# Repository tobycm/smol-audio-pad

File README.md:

# smol audio pad

a small keypad equipped with a xiao nrf52840 and a battery for portable and wireless usage, with a rotary encoder for input freedom!!

## PCB

## CAD

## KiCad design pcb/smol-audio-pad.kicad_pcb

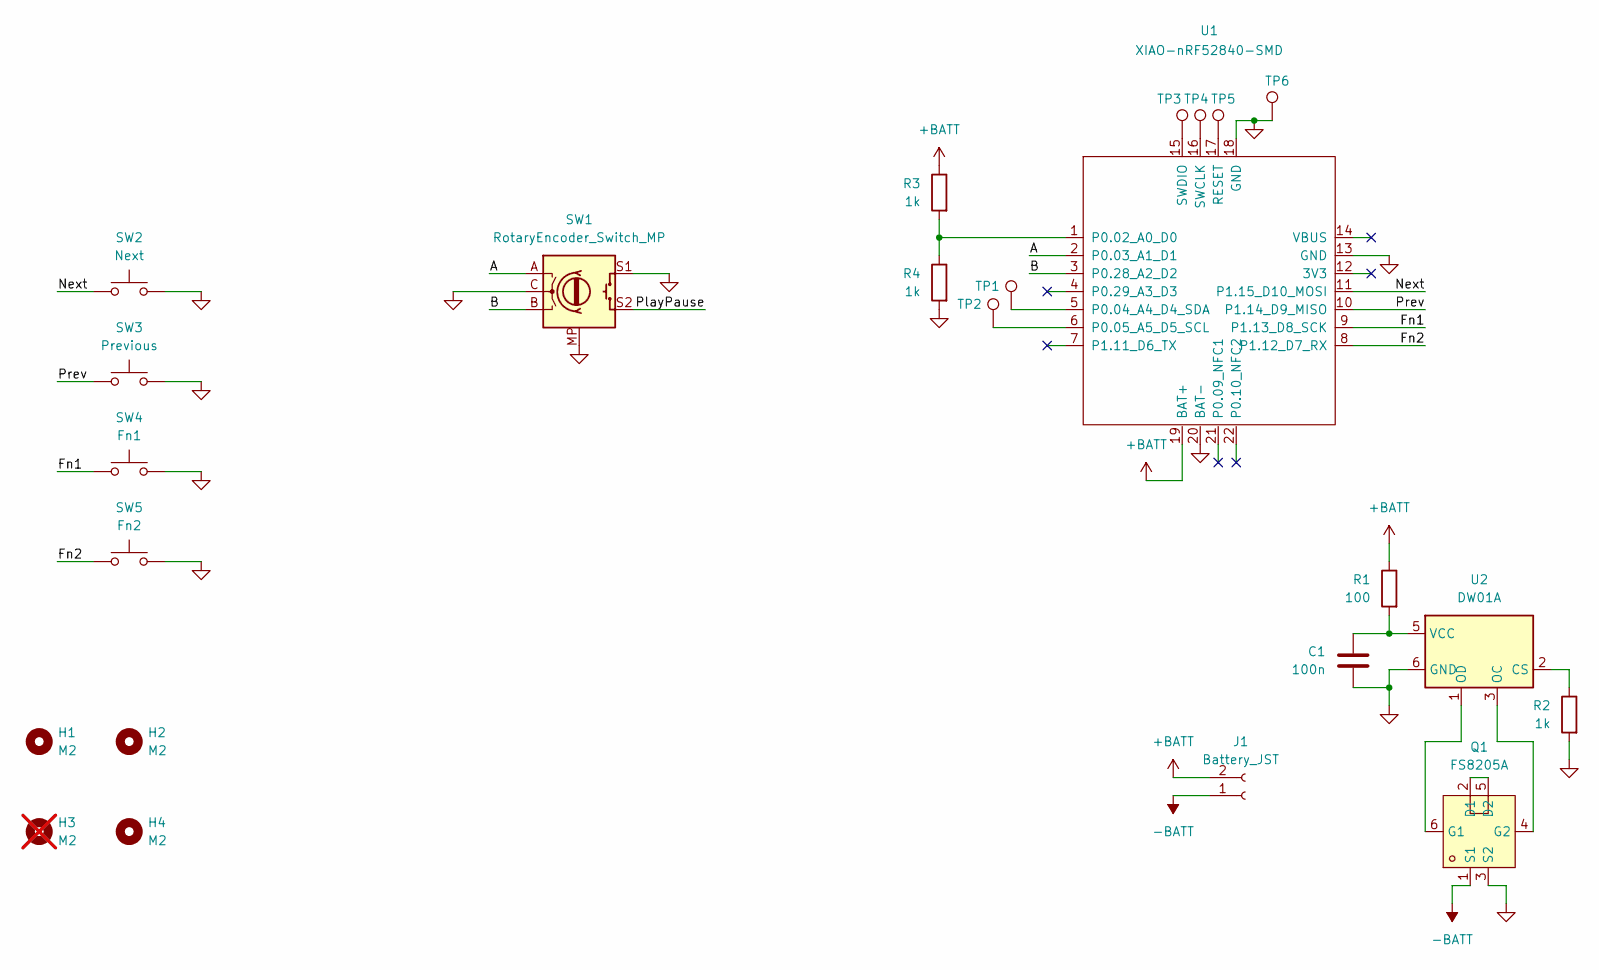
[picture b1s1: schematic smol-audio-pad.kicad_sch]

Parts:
C1: 100n; C_0603_1608Metric
H1, H2, H4: M2; MountingHole_2.2mm_M2_Pad
H3: M2; MountingHole_2.2mm_M2_Pad; not fitted
J1: Battery_JST; JST_PH_S2B-PH-K_1x02_P2.00mm_Horizontal
Q1: FS8205A; SOT-23-6; MPN FS8205A
R1: 100; R_0603_1608Metric
R2, R3, R4: 1k; R_0603_1608Metric
SW1: RotaryEncoder_Switch_MP; XDCR_PEC12R-4220F-S0024
SW2: Next; SW_Cherry_MX_1.00u_PCB
SW3: Previous; SW_Cherry_MX_1.00u_PCB
SW4: Fn1; SW_Cherry_MX_1.00u_PCB
SW5: Fn2; SW_Cherry_MX_1.00u_PCB
TP1, TP2, TP3, TP4, TP5, TP6: TestPoint; TestPoint_Pad_D2.0mm
U1: XIAO-nRF52840-SMD
U2: DW01A; SOT-23-6

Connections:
+BATT: J1.2, R1.1, R3.1, U1.19 (BAT+)
-BATT: J1.1, Q1.1 (S1)
/A: SW1.A, U1.2 (P0.03_A1_D1)
/B: SW1.B, U1.3 (P0.28_A2_D2)
/Fn1: SW4.1, U1.9 (P1.13_D8_SCK)
/Fn2: SW5.1, U1.8 (P1.12_D7_RX)
/Next: SW2.1, U1.11 (P1.15_D10_MOSI)
/PlayPause: SW1.S2
/Prev: SW3.1, U1.10 (P1.14_D9_MISO)
GND: C1.2, Q1.3 (S2), R2.2, R4.2, SW1.C, SW1.MP, SW1.S1, SW2.2, SW3.2, SW4.2, SW5.2, TP6.1 (1_1), U1.13 (GND), U1.18 (GND), U1.20 (BAT-), U2.6 (GND)
unnamed: Q1.2 (D1), Q1.5 (D2)
unnamed: Q1.6 (G1), U2.1 (OD)
unnamed: Q1.4 (G2), U2.3 (OC)
unnamed: R3.2, R4.1, U1.1 (P0.02_A0_D0)
unnamed: TP1.1 (1_1), U1.5 (P0.04_A4_D4_SDA)
unnamed: TP2.1 (1_1), U1.6 (P0.05_A5_D5_SCL)
unnamed: TP5.1 (1_1), U1.17 (RESET)
unnamed: TP4.1 (1_1), U1.16 (SWCLK)
unnamed: TP3.1 (1_1), U1.15 (SWDIO)
unnamed: R2.1, U2.2 (CS)
unnamed: C1.1, R1.2, U2.5 (VCC)

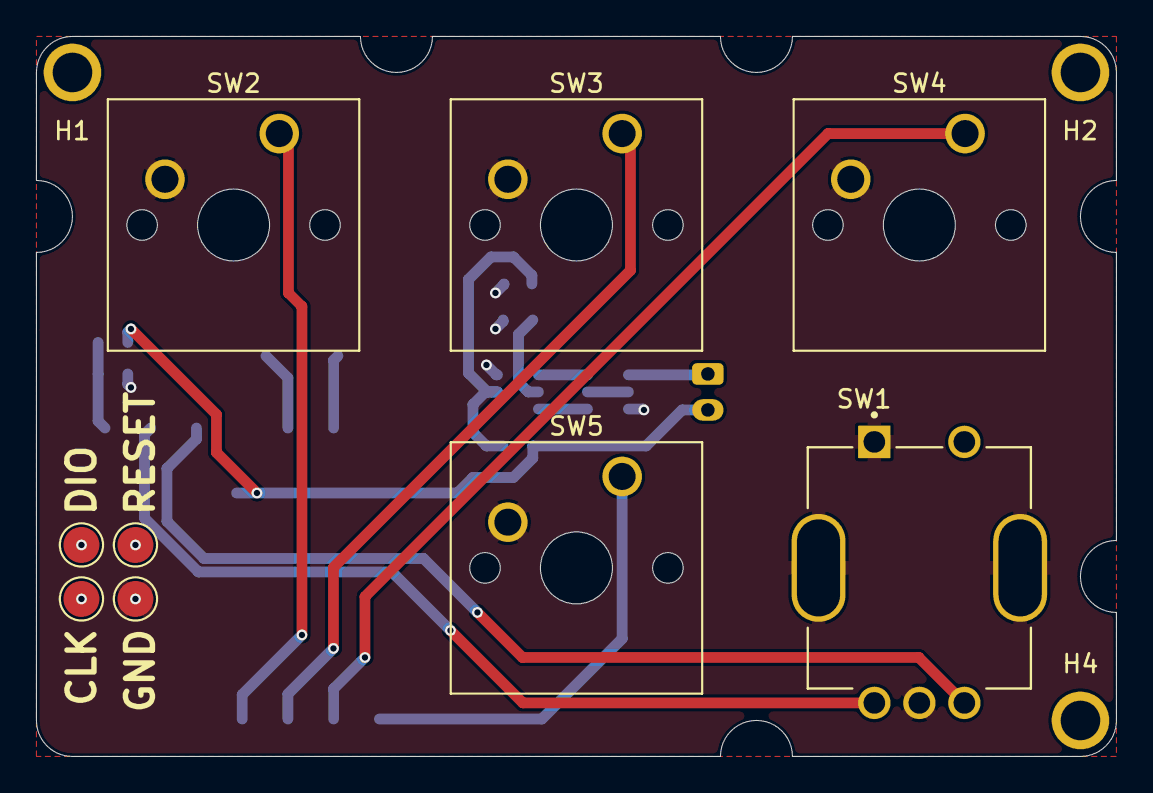
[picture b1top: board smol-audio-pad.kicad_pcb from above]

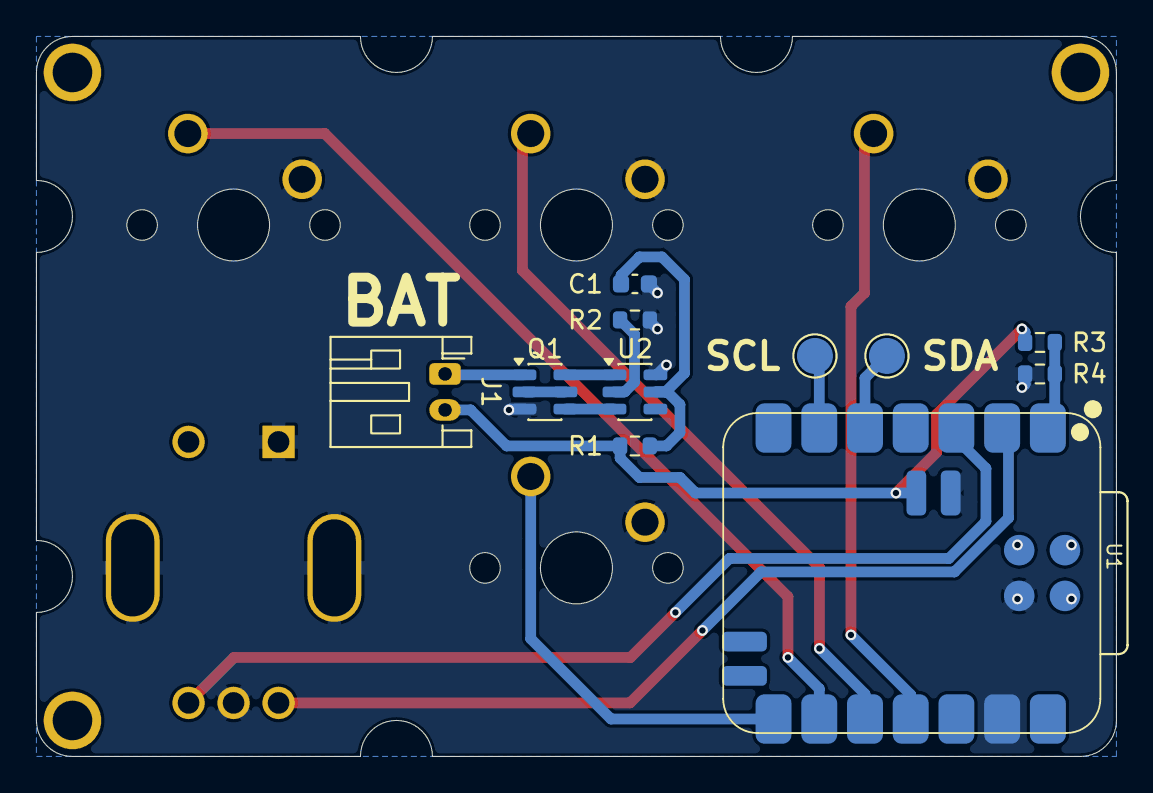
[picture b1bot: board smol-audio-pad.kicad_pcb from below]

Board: 2 copper layers, 60.0 x 40.0 mm, 23 parts (11 on the bottom side), 20 nets.

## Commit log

2026-06-19 pcb done!
2026-06-19 add cad stuff
2026-06-19 add bom and update readme
